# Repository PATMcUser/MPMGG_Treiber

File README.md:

# MPMGG_Treiber
Treiber für eine multi player multi goal HW auf Basis eines Raspberry Pi

Der Treiber ermöglicht die Verwendung der in der Dolumentation beschrieben en Hardware.
Es kann die Verwendung von Framebuffer-Treibern in Linux Betriebssystemen ersehen werden.
ZUgrunde liegt der Raspbarry Pi 3 als Entwicklungsboard und die Beschriebene Hardware.
Die Perepherie wird mittels SPI-Bus, GPIO und I²C-Bus angesteuert. Die Addressierung geschieht vollständig mittels der SPI-Portexpander.

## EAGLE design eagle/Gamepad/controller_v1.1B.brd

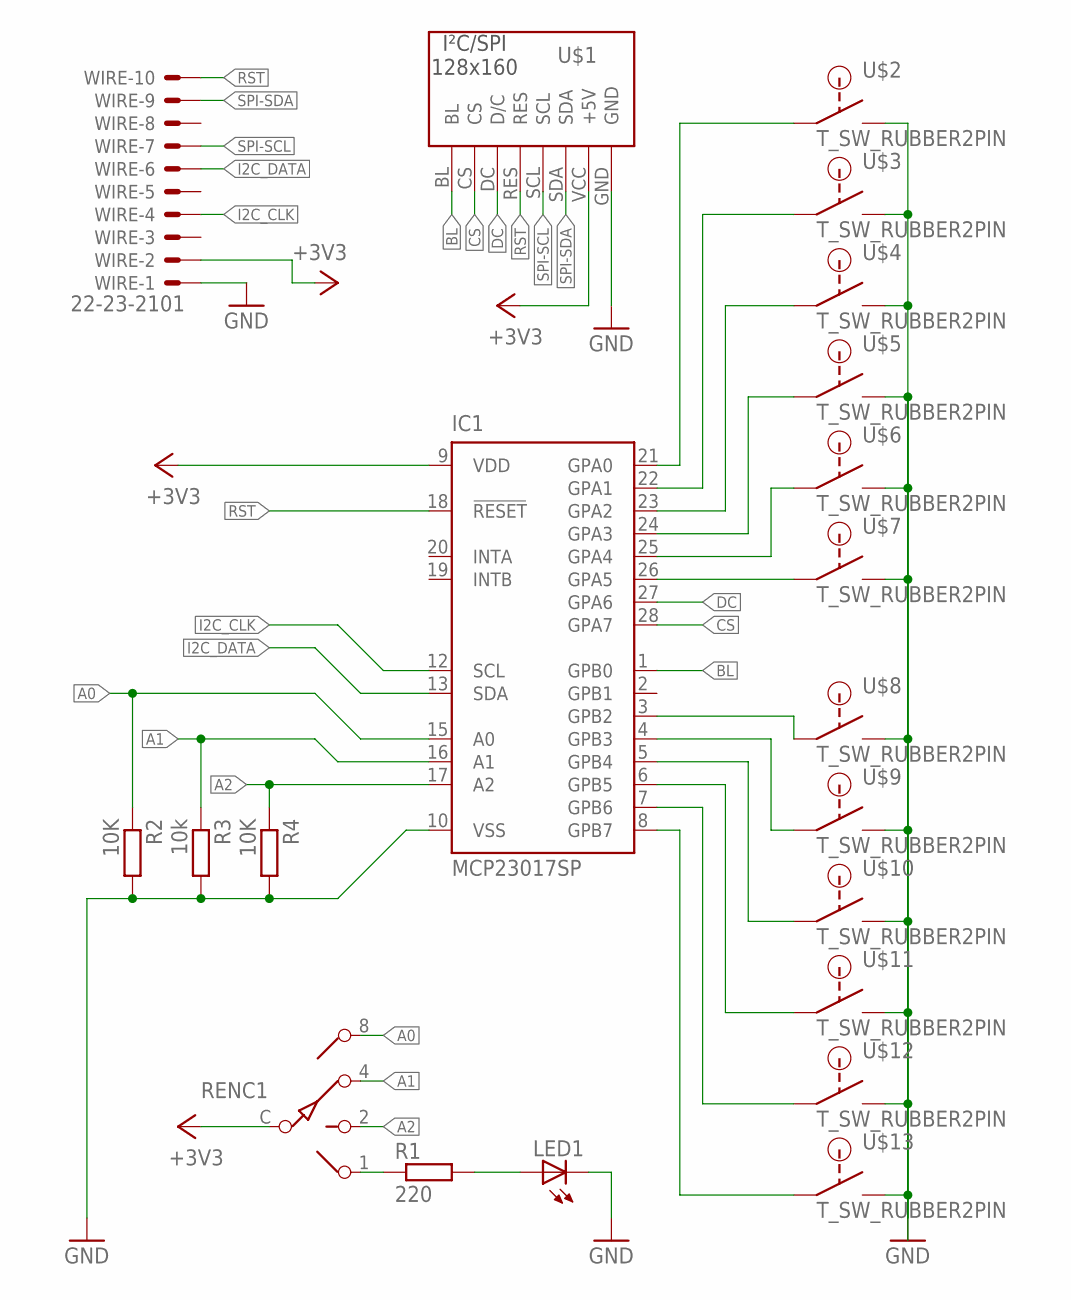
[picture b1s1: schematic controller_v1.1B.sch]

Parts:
IC1: MCP23017SP; DIL28-3
LED1: LED3MM
R1: 220; 0207/10
R2, R4: 10K; 0207/10
R3: 10k; 0207/10
RENC1: SW-C10
U$1: ST7735_128X160; 128X160_ST7735
U$2, U$3, U$4, U$5, U$6, U$7, U$8, U$9, U$10, U$11, U$12, U$13: T_SW_RUBBER2PIN; 2PIN
WIRE: 22-23-2101; MPN Wire-connection

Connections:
+3V3: IC1.9 (VDD), RENC1.C, U$1.VCC (+5V), WIRE.2
A0: IC1.15 (A0), R2.1, RENC1.8
A1: IC1.16 (A1), R3.1, RENC1.4
A2: IC1.17 (A2), R4.1, RENC1.2
BL: IC1.1 (GPB0), U$1.BL
CS: IC1.28 (GPA7), U$1.CS
DC: IC1.27 (GPA6), U$1.DC (D/C)
GND: IC1.10 (VSS), LED1.K (C), R2.2, R3.2, R4.2, U$1.GND, U$2.P$3, U$3.P$3, U$4.P$3, U$5.P$3, U$6.P$3, U$7.P$3, U$8.P$3, U$9.P$3, U$10.P$3, U$11.P$3, U$12.P$3, U$13.P$3, WIRE.1
I2C_CLK: IC1.12 (SCL), WIRE.4
I2C_DATA: IC1.13 (SDA), WIRE.6
unnamed: IC1.21 (GPA0), U$2.P$2
unnamed: R1.1, RENC1.1
unnamed: LED1.A, R1.2
unnamed: IC1.25 (GPA4), U$6.P$2
unnamed: IC1.24 (GPA3), U$5.P$2
unnamed: IC1.23 (GPA2), U$4.P$2
unnamed: IC1.22 (GPA1), U$3.P$2
RST: IC1.18 (!RESET), U$1.RES, WIRE.10
SPI-SCL: U$1.SCL, WIRE.7
SPI-SDA: U$1.SDA, WIRE.9
SW6: IC1.26 (GPA5), U$7.P$2
SW7: IC1.3 (GPB2), U$8.P$2
SW8: IC1.4 (GPB3), U$9.P$2
SW9: IC1.5 (GPB4), U$10.P$2
SW10: IC1.6 (GPB5), U$11.P$2
SW11: IC1.7 (GPB6), U$12.P$2
SW12: IC1.8 (GPB7), U$13.P$2

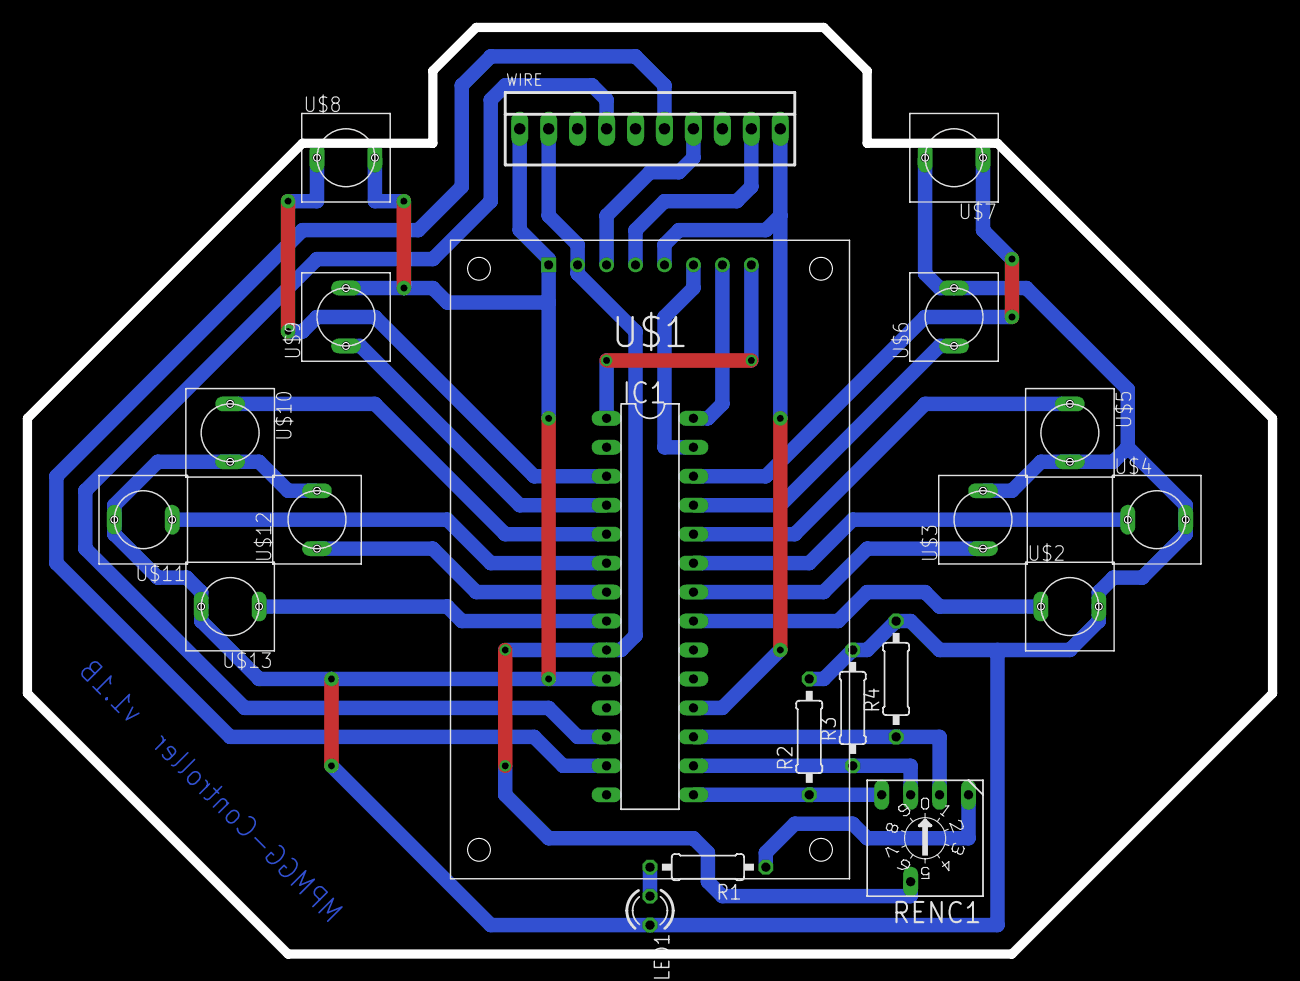
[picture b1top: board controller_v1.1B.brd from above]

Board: 2 copper layers, 109.2 x 81.3 mm, 21 parts (0 on the bottom side), 27 nets.

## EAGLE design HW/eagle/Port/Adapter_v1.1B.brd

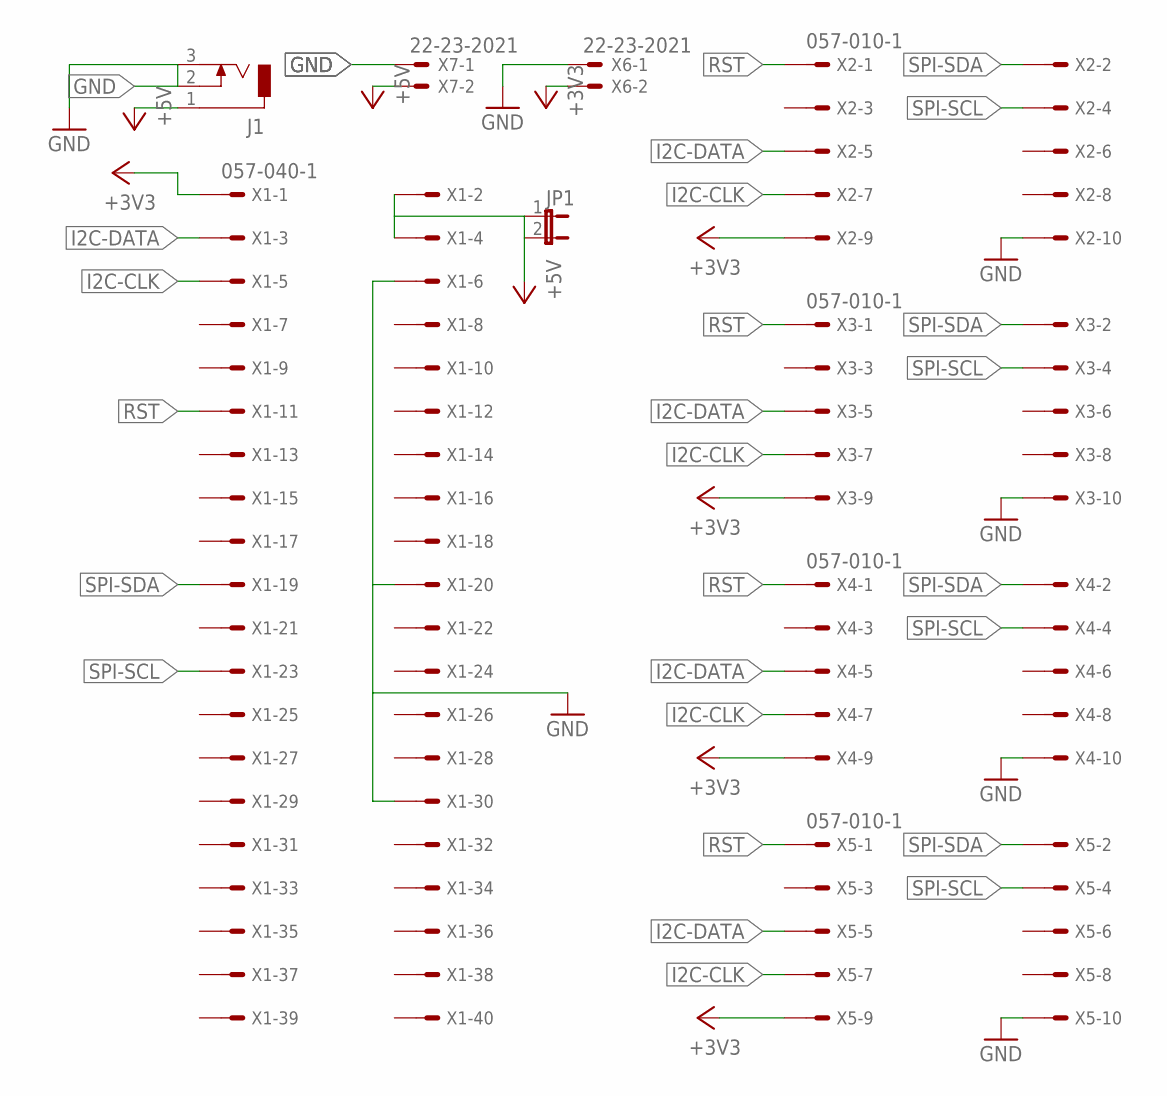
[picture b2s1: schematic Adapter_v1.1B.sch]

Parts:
J1: DCJ0303
JP1: JP1E; JP1
X1: 057-040-1
X2, X3, X4, X5: 057-010-1
X6, X7: 22-23-2021

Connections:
+3V3: X1.1, X2.9, X3.9, X4.9, X5.9, X6.2
+5V: J1.1, JP1.1, JP1.2, X1.2, X1.4, X7.2
GND: J1.2, J1.3, X1.6, X1.20, X1.30, X2.10, X3.10, X4.10, X5.10, X6.1, X7.1
I2C-CLK: X1.5, X2.7, X3.7, X4.7, X5.7
I2C-DATA: X1.3, X2.5, X3.5, X4.5, X5.5
RST: X1.11, X2.1, X3.1, X4.1, X5.1
SPI-SCL: X1.23, X2.4, X3.4, X4.4, X5.4
SPI-SDA: X1.19, X2.2, X3.2, X4.2, X5.2

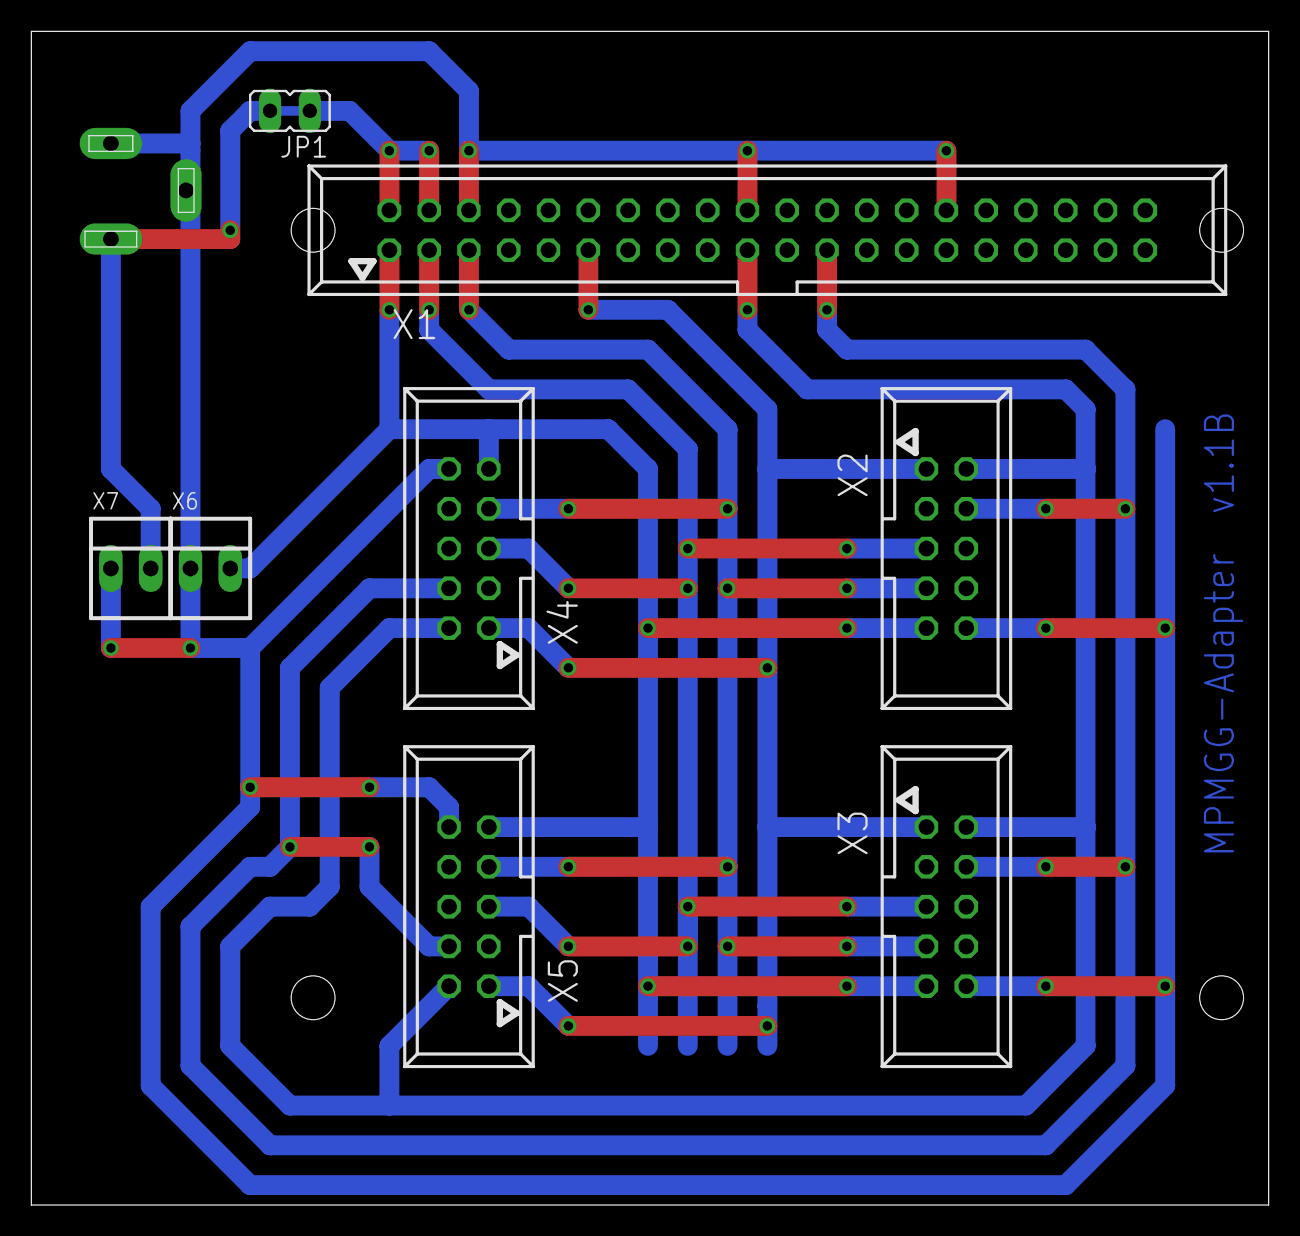
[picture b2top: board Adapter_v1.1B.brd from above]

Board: 2 copper layers, 79.0 x 74.9 mm, 9 parts (1 on the bottom side), 8 nets.

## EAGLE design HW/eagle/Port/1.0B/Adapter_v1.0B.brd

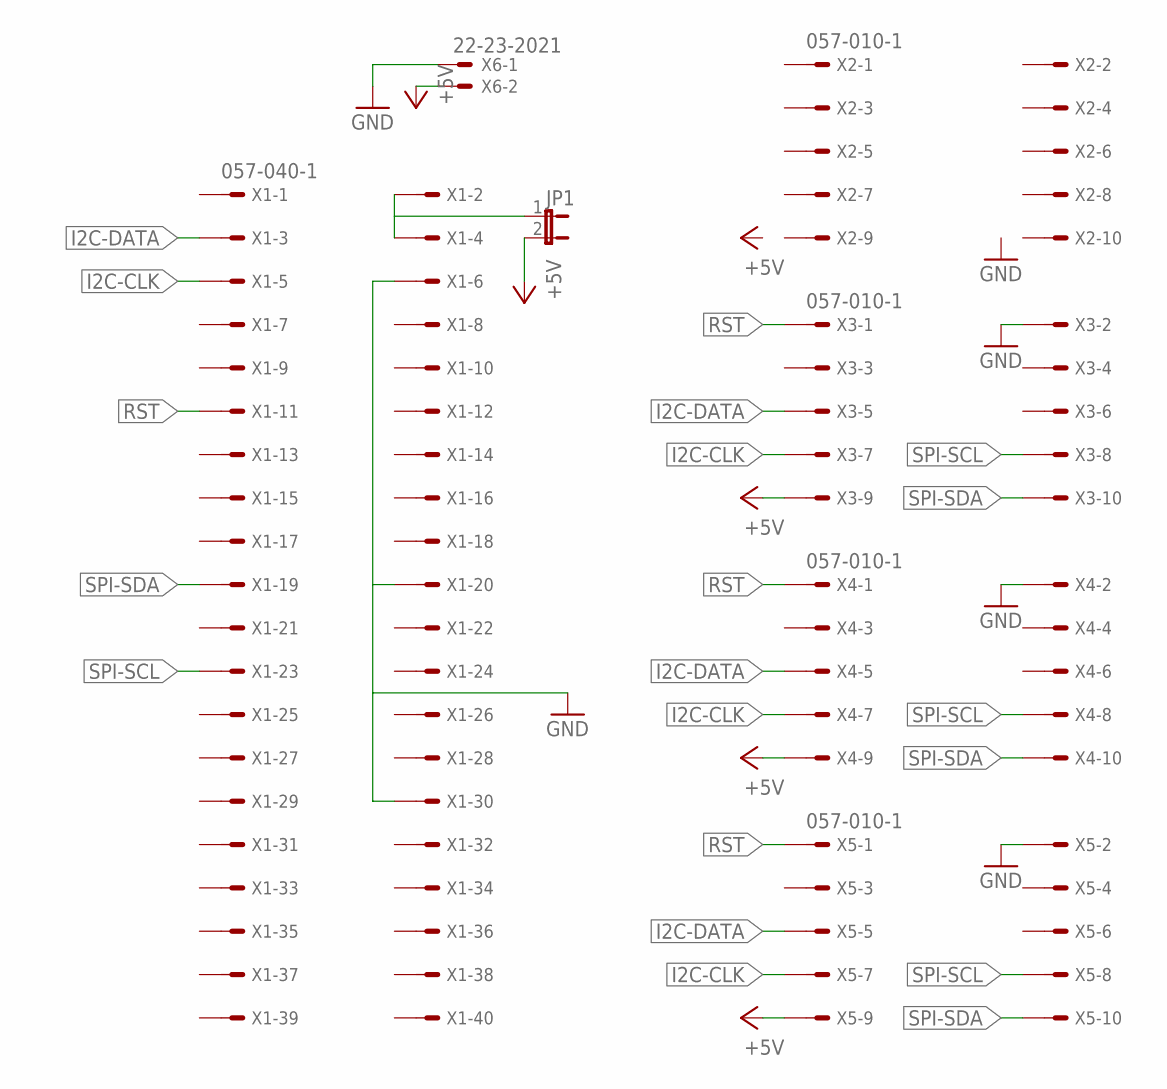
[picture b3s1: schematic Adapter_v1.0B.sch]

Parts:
JP1: JP1E; JP1
X1: 057-040-1
X2, X3, X4, X5: 057-010-1
X6: 22-23-2021

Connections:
+5V: JP1.2, X2.9, X3.9, X4.9, X5.9, X6.2
GND: X1.6, X1.20, X1.30, X2.2, X3.2, X4.2, X5.2, X6.1
I2C-CLK: X1.5, X2.7, X3.7, X4.7, X5.7
I2C-DATA: X1.3, X2.5, X3.5, X4.5, X5.5
unnamed: JP1.1, X1.2, X1.4
RST: X1.11, X2.1, X3.1, X4.1, X5.1
SPI-SCL: X1.23, X2.8, X3.8, X4.8, X5.8
SPI-SDA: X1.19, X2.10, X3.10, X4.10, X5.10

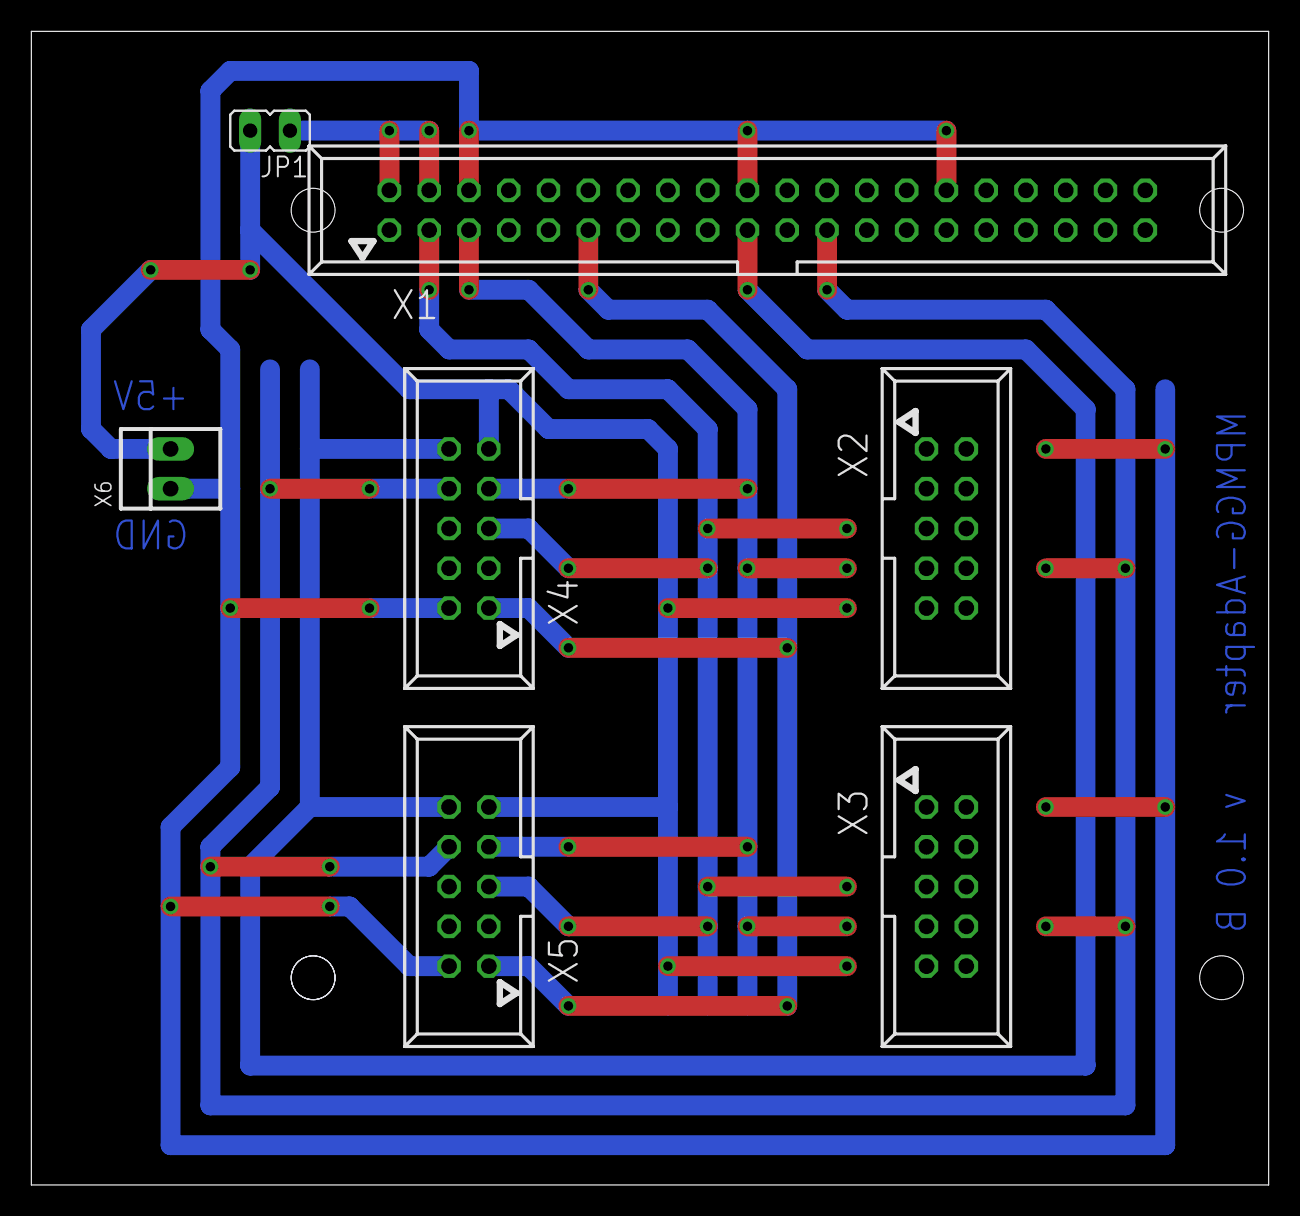
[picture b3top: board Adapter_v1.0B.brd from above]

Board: 2 copper layers, 79.0 x 73.7 mm, 7 parts (0 on the bottom side), 8 nets.

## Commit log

2017-05-24 Structure with schematics
2017-06-06 First testable
2017-06-06 Update Makefile
2018-06-19 Final
